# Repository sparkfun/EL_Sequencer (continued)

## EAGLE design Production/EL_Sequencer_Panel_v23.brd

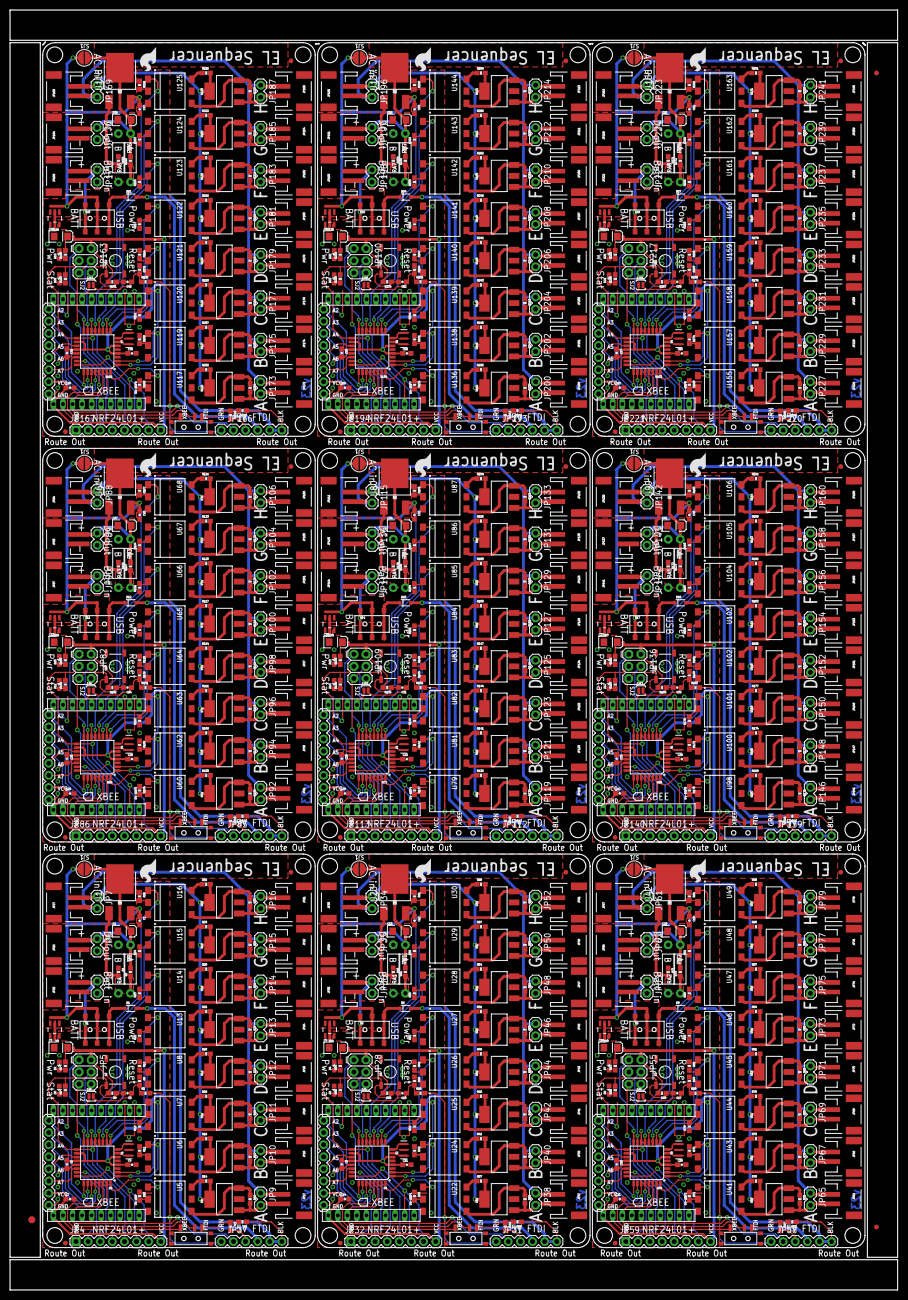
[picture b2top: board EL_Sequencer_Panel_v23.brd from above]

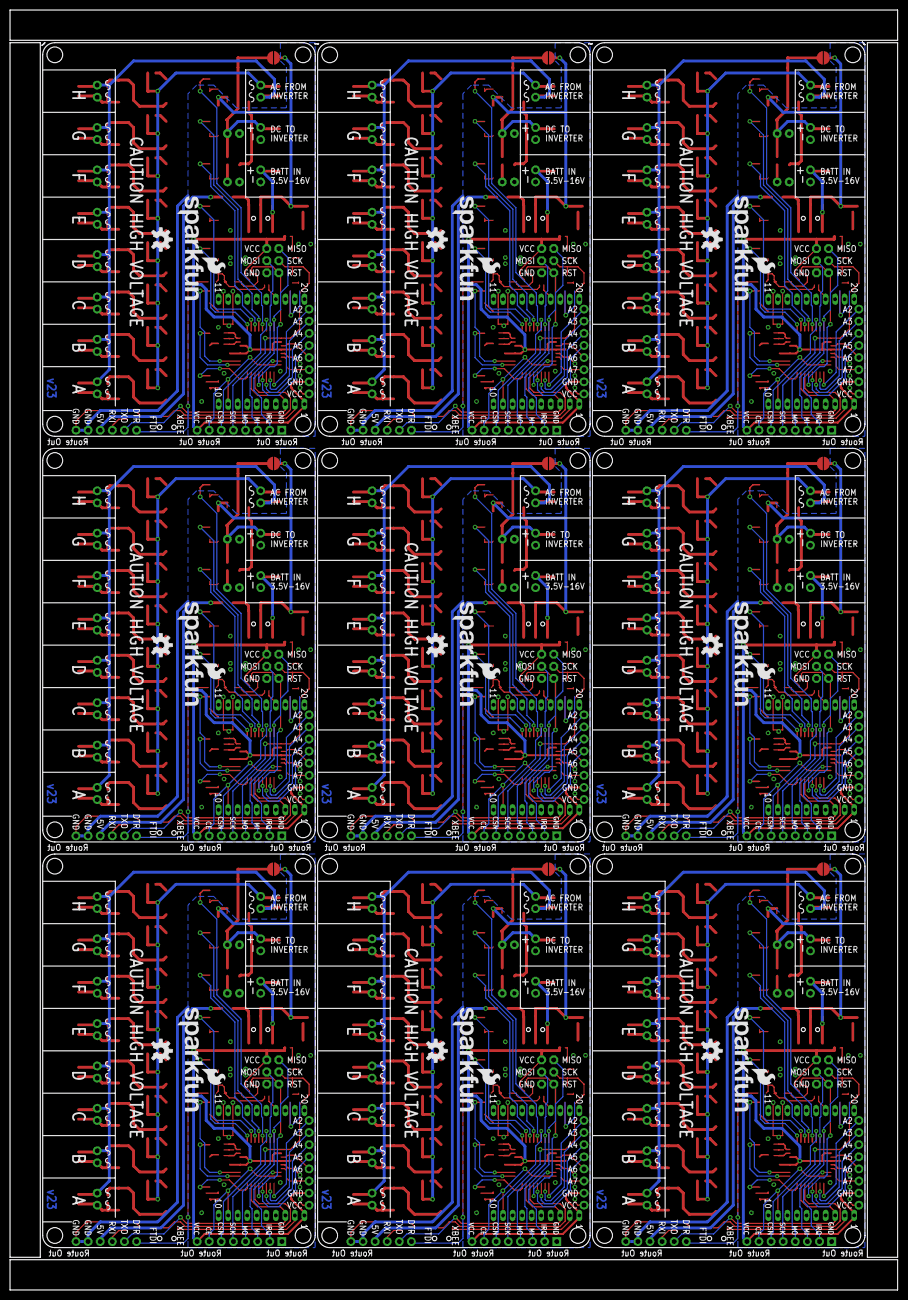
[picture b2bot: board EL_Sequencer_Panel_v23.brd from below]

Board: 2 copper layers, 186.2 x 268.5 mm, 957 parts (18 on the bottom side), 675 nets.

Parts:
C1, C4, C5, C6, C7, C8, C10, C11, C12, C14, C15, C17, C18, C19, C21, C22, C24, C25, C26, C28, C29, C31, C32, C33, C35, C36, C38, C39, C40, C42, C43, C45, C46, C47, C49, C50, C52, C53, C54, C56, C57, C59, C60, C61, C63: 0.1uF; 0603-CAP
C2, C3, C9, C13, C16, C20, C23, C27, C30, C34, C37, C41, C44, C48, C51, C55, C58, C62: 10uF; EIA3216
D1, D6, D9, D12, D15, D18, D21, D24, D27: PMEG4005EJ; SOD-323
D2, D4, D7, D10, D13, D16, D19, D22, D25: RED; LED-0603
D3, D5, D8, D11, D14, D17, D20, D23, D26: BLUE; LED-0603
E$1: FIDUCIAL-1.5X3
E$4, E$5: FIDUCIAL-1X2
FID1, FID2, FID3, FID4, FID5, FID6, FID7, FID8, FID9, FID10, FID11, FID12, FID13, FID14, FID15, FID16, FID17, FID18: FIDUCIAL1X2; FIDUCIAL-1X2
JP1, JP6, JP7, JP9, JP10, JP11, JP12, JP13, JP14, JP15, JP16, JP34, JP35, JP36, JP38, JP40, JP42, JP44, JP46, JP48, JP50, JP52, JP61, JP62, JP63, JP65, JP67, JP69, JP71, JP73, JP75, JP77, JP79, JP88, JP89, JP90, JP92, JP94, JP96, JP98, JP100, JP102, JP104, JP106, JP115, JP116, JP117, JP119, JP121, JP123, JP125, JP127, JP129, JP131, JP133, JP142, JP143, JP144, JP146, JP148, JP150, JP152, JP154, JP156, JP158, JP160, JP169, JP170, JP171, JP173, JP175, JP177, JP179, JP181, JP183, JP185, JP187, JP196, JP197, JP198, JP200, JP202, JP204, JP206, JP208, JP210, JP212, JP214, JP223, JP224, JP225, JP227, JP229, JP231, JP233, JP235, JP237, JP239, JP241: M02PTH; 1X02
JP2, JP53, JP80, JP107, JP134, JP161, JP188, JP215, JP242: I/O; 1X08_ROUND
JP3, JP31, JP58, JP85, JP112, JP139, JP166, JP193, JP220: 5V_FTDI; FTDI_BASIC
JP4, JP32, JP59, JP86, JP113, JP140, JP167, JP194, JP221: nRF24L01; 1X08
JP5, JP28, JP55, JP82, JP109, JP136, JP163, JP190, JP217: PROG; 2X3
JP8, JP54, JP81, JP108, JP135, JP162, JP189, JP216, JP243: SFE_LOGO_FLAME.2_INCH; SFE_LOGO_FLAME_.2
JP17, JP18, JP19, JP20, JP21, JP22, JP23, JP24, JP37, JP39, JP41, JP43, JP45, JP47, JP49, JP51, JP64, JP66, JP68, JP70, JP72, JP74, JP76, JP78, JP91, JP93, JP95, JP97, JP99, JP101, JP103, JP105, JP118, JP120, JP122, JP124, JP126, JP128, JP130, JP132, JP145, JP147, JP149, JP151, JP153, JP155, JP157, JP159, JP172, JP174, JP176, JP178, JP180, JP182, JP184, JP186, JP199, JP201, JP203, JP205, JP207, JP209, JP211, JP213, JP226, JP228, JP230, JP232, JP234, JP236, JP238, JP240: M02-JST-2MM-SMT; JST-2-SMD
JP25, JP33, JP60, JP87, JP114, JP141, JP168, JP195, JP222: Battery; JST-2-SMD
JP26, JP29, JP56, JP83, JP110, JP137, JP164, JP191, JP218: DC-OUTPUT; JST-2-SMD
JP27, JP30, JP57, JP84, JP111, JP138, JP165, JP192, JP219: AC-INPUT; JST-2-SMD
R1, R10, R11, R12, R13, R22, R23, R24, R25, R38, R40, R43, R46, R49, R52, R55, R58, R61, R71, R73, R76, R79, R82, R85, R88, R91, R94, R104, R106, R109, R112, R115, R118, R121, R124, R127, R137, R139, R142, R145, R148, R151, R154, R157, R160, R170, R172, R175, R178, R181, R184, R187, R190, R193, R203, R205, R208, R211, R214, R217, R220, R223, R226, R236, R238, R241, R244, R247, R250, R253, R256, R259, R269, R271, R274, R277, R280, R283, R286, R289, R292: 390; 0603-RES
R2, R41, R74, R107, R140, R173, R206, R239, R272: 240; 0603-RES
R3, R5, R7, R9, R34, R35, R64, R65, R67, R68, R97, R98, R100, R101, R130, R131, R133, R134, R163, R164, R166, R167, R196, R197, R199, R200, R229, R230, R232, R233, R262, R263, R265, R266, R295, R296: 1K; 0603-RES
R4, R6, R63, R66, R96, R99, R129, R132, R162, R165, R195, R198, R228, R231, R261, R264, R294, R297: 2K; 0603-RES
R8, R36, R69, R102, R135, R168, R201, R234, R267: 10K; 0603-RES
R14, R15, R16, R17, R18, R19, R20, R21, R26, R27, R28, R29, R30, R31, R32, R33, R37, R39, R42, R44, R45, R47, R48, R50, R51, R53, R54, R56, R57, R59, R60, R62, R70, R72, R75, R77, R78, R80, R81, R83, R84, R86, R87, R89, R90, R92, R93, R95, R103, R105, R108, R110, R111, R113, R114, R116, R117, R119, R120, R122, R123, R125, R126, R128, R136, R138, R141, R143, R144, R146, R147, R149, R150, R152, R153, R155, R156, R158, R159, R161, R169, R171, R174, R176, R177, R179, R180, R182, R183, R185, R186, R188, R189, R191, R192, R194, R202, R204, R207, R209, R210, R212, R213, R215, R216, R218, R219, R221, R222, R224, R225, R227, R235, R237, R240, R242, R243, R245, R246, R248, R249, R251, R252, R254, R255, R257, R258, R260, R268, R270, R273, R275, R276, R278, R279, R281, R282, R284, R285, R287, R288, R290, R291, R293: 330; 0603-RES
RA, RA1, RA2, RA3, RA4, RA5, RA6, RA7, RA8: A; AXIAL-0.4
RB, RB1, RB2, RB3, RB4, RB5, RB6, RB7, RB8: B; AXIAL-0.4
S1, S5, S8, S11, S14, S17, S20, S23, S26: DPDT; AYZ0202
S2, S4, S7, S10, S13, S16, S19, S22, S25: RESET; TACTILE-SWITCH-SMD
S3, S6, S9, S12, S15, S18, S21, S24, S27: SWITCH_SPDT; KPS-1290
SJ1, SJ3, SJ5, SJ7, SJ9, SJ11, SJ13, SJ15, SJ17: JUMPER-PAD-2-NOROUND; PAD-JUMPER-2-NO_YES_SILK_ROUND
SJ2, SJ4, SJ6, SJ8, SJ10, SJ12, SJ14, SJ16, SJ18: JUMPER-PAD-2-NOYES_SILK; PAD-JUMPER-2-NO_YES_SILK
U1, U23, U42, U61, U80, U99, U118, U137, U156: LM317; V-REG_DPACK
U2, U21, U40, U59, U78, U97, U116, U135, U154: MIC5219 3.3V; SOT23-5
U3, U4, U39, U58, U77, U96, U115, U134, U153: ATMEGA328P_TQFP; TQFP32-08
U4-DNP, U4-DNP1, U4-DNP2, U4-DNP3, U4-DNP4, U4-DNP5, U4-DNP6, U4-DNP7, U4-DNP8: XBEE HEADER; XBEE-LONGPAD
U5, U6, U7, U8, U13, U14, U15, U16, U22, U24, U25, U26, U27, U28, U29, U30, U41, U43, U44, U45, U46, U47, U48, U49, U60, U62, U63, U64, U65, U66, U67, U68, U79, U81, U82, U83, U84, U85, U86, U87, U98, U100, U101, U102, U103, U104, U105, U106, U117, U119, U120, U121, U122, U123, U124, U125, U136, U138, U139, U140, U141, U142, U143, U144, U155, U157, U158, U159, U160, U161, U162, U163: MOC3063S; DIP8SMD
U9, U10, U11, U12, U17, U18, U19, U20, U31, U32, U33, U34, U35, U36, U37, U38, U50, U51, U52, U53, U54, U55, U56, U57, U69, U70, U71, U72, U73, U74, U75, U76, U88, U89, U90, U91, U92, U93, U94, U95, U107, U108, U109, U110, U111, U112, U113, U114, U126, U127, U128, U129, U130, U131, U132, U133, U145, U146, U147, U148, U149, U150, U151, U152, U164, U165, U166, U167, U168, U169, U170, U171: Z0103MN; SOT223
U$1, U$12, U$18, U$24, U$30, U$36, U$42, U$48, U$54: OSHW-LOGOM; OSHW-LOGO-M
U$2, U$3, U$13, U$19, U$25, U$31, U$37, U$43, U$49: SFE_LOGO_NAME_FLAME.2_INCH; SFE_LOGO_NAME_FLAME_.2
U$4, U$5, U$6, U$7, U$8, U$9, U$10, U$11, U$14, U$15, U$16, U$17, U$20, U$21, U$22, U$23, U$26, U$27, U$28, U$29, U$32, U$33, U$34, U$35, U$38, U$39, U$40, U$41, U$44, U$45, U$46, U$47, U$50, U$51, U$52, U$53: STAND-OFF
Y1, Y2, Y3, Y4, Y5, Y6, Y7, Y8, Y9: 8MHZ; RESONATOR-SMD

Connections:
5VUSB: D1.A, JP3.VCC
5VUSB1: D6.A, JP31.VCC
5VUSB2: D9.A, JP58.VCC
5VUSB3: D12.A, JP85.VCC
5VUSB4: D15.A, JP112.VCC
5VUSB5: D18.A, JP139.VCC
5VUSB6: D21.A, JP166.VCC
5VUSB7: D24.A, JP193.VCC
5VUSB8: D27.A, JP220.VCC
ADC_1: JP53.8, U4.25
ADC_2: JP2.8, U3.25
ADC_3: JP2.7, U3.26
ADC_4: JP2.6, U3.27
ADC_5: JP2.5, U3.28
ADC_6: JP53.7, U4.26
ADC_6*: JP2.4, U3.19
ADC_6*1: JP53.4, U4.19
ADC_6*2: JP80.4, U39.19
ADC_6*3: JP107.4, U58.19
ADC_6*4: JP134.4, U77.19
ADC_6*5: JP161.4, U96.19
ADC_6*6: JP188.4, U115.19
ADC_6*7: JP215.4, U134.19
ADC_6*8: JP242.4, U153.19
ADC_7: JP53.6, U4.27
ADC_7*: JP2.3, U3.22
ADC_7*1: JP53.3, U4.22
ADC_7*2: JP80.3, U39.22
ADC_7*3: JP107.3, U58.22
ADC_7*4: JP134.3, U77.22
ADC_7*5: JP161.3, U96.22
ADC_7*6: JP188.3, U115.22
ADC_7*7: JP215.3, U134.22
ADC_7*8: JP242.3, U153.22
ADC_8: JP53.5, U4.28
ADC_9: JP80.8, U39.25
ADC_10: JP80.7, U39.26
ADC_11: JP80.6, U39.27
ADC_12: JP80.5, U39.28
ADC_13: JP107.8, U58.25
ADC_14: JP107.7, U58.26
ADC_15: JP107.6, U58.27
ADC_16: JP107.5, U58.28
ADC_17: JP134.8, U77.25
ADC_18: JP134.7, U77.26
ADC_19: JP134.6, U77.27
ADC_20: JP134.5, U77.28
ADC_21: JP161.8, U96.25
ADC_22: JP161.7, U96.26
ADC_23: JP161.6, U96.27
ADC_24: JP161.5, U96.28
ADC_25: JP188.8, U115.25
ADC_26: JP188.7, U115.26
ADC_27: JP188.6, U115.27
ADC_28: JP188.5, U115.28
ADC_29: JP215.8, U134.25
ADC_30: JP215.7, U134.26
ADC_31: JP215.6, U134.27
ADC_32: JP215.5, U134.28
ADC_33: JP242.8, U153.25
ADC_34: JP242.7, U153.26
ADC_35: JP242.6, U153.27
ADC_36: JP242.5, U153.28
CE/SLEEP: JP4.7, U3.24, U4-DNP.9
CE/SLEEP1: JP32.7, U4.24, U4-DNP1.9
CE/SLEEP2: JP59.7, U4-DNP2.9, U39.24
CE/SLEEP3: JP86.7, U4-DNP3.9, U58.24
CE/SLEEP4: JP113.7, U4-DNP4.9, U77.24
CE/SLEEP5: JP140.7, U4-DNP5.9, U96.24
CE/SLEEP6: JP167.7, U4-DNP6.9, U115.24
CE/SLEEP7: JP194.7, U4-DNP7.9, U134.24
CE/SLEEP8: JP221.7, U4-DNP8.9, U153.24
CSN: JP4.6, U3.14
CSN1: JP32.6, U4.14
CSN2: JP59.6, U39.14
CSN3: JP86.6, U58.14
CSN4: JP113.6, U77.14
CSN5: JP140.6, U96.14
CSN6: JP167.6, U115.14
CSN7: JP194.6, U134.14
CSN8: JP221.6, U153.14
DIO_VBUS: D1.C, S1.3, S1.6
DIO_VBUS1: D6.C, S5.3, S5.6
DIO_VBUS2: D9.C, S8.3, S8.6
DIO_VBUS3: D12.C, S11.3, S11.6
DIO_VBUS4: D15.C, S14.3, S14.6
DIO_VBUS5: D18.C, S17.3, S17.6
DIO_VBUS6: D21.C, S20.3, S20.6
DIO_VBUS7: D24.C, S23.3, S23.6
DIO_VBUS8: D27.C, S26.3, S26.6
DTR: C5.1, R5.1, R6.2, SJ2.2
DTR1: C10.1, R65.1, R66.2, SJ4.2
DTR2: C17.1, R98.1, R99.2, SJ6.2
DTR3: C24.1, R131.1, R132.2, SJ8.2
DTR4: C31.1, R164.1, R165.2, SJ10.2
DTR5: C38.1, R197.1, R198.2, SJ12.2
DTR6: C45.1, R230.1, R231.2, SJ14.2
DTR7: C52.1, R263.1, R264.2, SJ16.2
DTR8: C59.1, R296.1, R297.2, SJ18.2
EL_A: U3.32, U5.1
EL_A1: U4.32, U22.1
EL_A2: U39.32, U41.1
EL_A3: U58.32, U60.1
EL_A4: U77.32, U79.1
EL_A5: U96.32, U98.1
EL_A6: U115.32, U117.1
EL_A7: U134.32, U136.1
EL_A8: U153.32, U155.1
EL_B: U3.1, U6.1
EL_B1: U4.1, U24.1
EL_B2: U39.1, U43.1
EL_B3: U58.1, U62.1
EL_B4: U77.1, U81.1
EL_B5: U96.1, U100.1
EL_B6: U115.1, U119.1
EL_B7: U134.1, U138.1
EL_B8: U153.1, U157.1
EL_C: U3.2, U7.1
EL_C1: U4.2, U25.1
EL_C2: U39.2, U44.1
EL_C3: U58.2, U63.1
EL_C4: U77.2, U82.1
EL_C5: U96.2, U101.1
EL_C6: U115.2, U120.1
EL_C7: U134.2, U139.1
EL_C8: U153.2, U158.1
EL_D: U3.9, U8.1
EL_D1: U4.9, U26.1
EL_D2: U39.9, U45.1
EL_D3: U58.9, U64.1
EL_D4: U77.9, U83.1
EL_D5: U96.9, U102.1
EL_D6: U115.9, U121.1
EL_D7: U134.9, U140.1
EL_D8: U153.9, U159.1
EL_E: U3.10, U13.1
EL_E1: U4.10, U27.1
EL_E2: U39.10, U46.1
EL_E3: U58.10, U65.1
EL_E4: U77.10, U84.1
EL_E5: U96.10, U103.1
EL_E6: U115.10, U122.1
EL_E7: U134.10, U141.1
EL_E8: U153.10, U160.1
EL_F: U3.11, U14.1
EL_F1: U4.11, U28.1
EL_F2: U39.11, U47.1
EL_F3: U58.11, U66.1
EL_F4: U77.11, U85.1
EL_F5: U96.11, U104.1
EL_F6: U115.11, U123.1
EL_F7: U134.11, U142.1
EL_F8: U153.11, U161.1
EL_G: U3.12, U15.1
EL_G1: U4.12, U29.1
EL_G2: U39.12, U48.1
EL_G3: U58.12, U67.1
EL_G4: U77.12, U86.1
EL_G5: U96.12, U105.1
EL_G6: U115.12, U124.1
EL_G7: U134.12, U143.1
EL_G8: U153.12, U162.1
EL_H: U3.13, U16.1
EL_H1: U4.13, U30.1
EL_H2: U39.13, U49.1
EL_H3: U58.13, U68.1
EL_H4: U77.13, U87.1
EL_H5: U96.13, U106.1
EL_H6: U115.13, U125.1
EL_H7: U134.13, U144.1
EL_H8: U153.13, U163.1
FTDI_DTR: JP3.DTR, R5.2
FTDI_DTR1: JP31.DTR, R65.2
FTDI_DTR2: JP58.DTR, R98.2
FTDI_DTR3: JP85.DTR, R131.2
FTDI_DTR4: JP112.DTR, R164.2
FTDI_DTR5: JP139.DTR, R197.2
FTDI_DTR6: JP166.DTR, R230.2
FTDI_DTR7: JP193.DTR, R263.2
FTDI_DTR8: JP220.DTR, R296.2
FTDI_RXI: JP3.TXO, R3.2
FTDI_RXI1: JP31.TXO, R64.2
FTDI_RXI2: JP58.TXO, R97.2
FTDI_RXI3: JP85.TXO, R130.2
FTDI_RXI4: JP112.TXO, R163.2
FTDI_RXI5: JP139.TXO, R196.2
FTDI_RXI6: JP166.TXO, R229.2
FTDI_RXI7: JP193.TXO, R262.2
FTDI_RXI8: JP220.TXO, R295.2
GND: C1.2, C2.C, C3.C, C4.2, C6.2, C7.2, D2.C, D3.C, JP1.2, JP2.1, JP3.CTS, JP3.GND, JP4.1, JP5.6, JP6.2, JP25.1, JP26.1, R1.1, R4.1, R6.1, R10.1, R11.1, R12.1, R13.1, R22.1, R23.1, R24.1, R25.1, RB.P$1, S2.3, U2.2, U3.3, U3.5, U3.21, U4-DNP.10, Y1.2
GND1: C8.2, C9.C, C11.2, C12.2, C13.C, C14.2, D4.C, D5.C, JP28.6, JP29.1, JP31.CTS, JP31.GND, JP32.1, JP33.1, JP35.2, JP36.2, JP53.1, R38.1, R40.1, R43.1, R46.1, R49.1, R52.1, R55.1, R58.1, R61.1, R63.1, R66.1, RB1.P$1, S4.3, U4.3, U4.5, U4.21, U4-DNP1.10, U21.2, Y2.2
GND2: C15.2, C16.C, C18.2, C19.2, C20.C, C21.2, D7.C, D8.C, JP55.6, JP56.1, JP58.CTS, JP58.GND, JP59.1, JP60.1, JP62.2, JP63.2, JP80.1, R71.1, R73.1, R76.1, R79.1, R82.1, R85.1, R88.1, R91.1, R94.1, R96.1, R99.1, RB2.P$1, S7.3, U4-DNP2.10, U39.3, U39.5, U39.21, U40.2, Y3.2
GND3: C22.2, C23.C, C25.2, C26.2, C27.C, C28.2, D10.C, D11.C, JP82.6, JP83.1, JP85.CTS, JP85.GND, JP86.1, JP87.1, JP89.2, JP90.2, JP107.1, R104.1, R106.1, R109.1, R112.1, R115.1, R118.1, R121.1, R124.1, R127.1, R129.1, R132.1, RB3.P$1, S10.3, U4-DNP3.10, U58.3, U58.5, U58.21, U59.2, Y4.2
GND4: C29.2, C30.C, C32.2, C33.2, C34.C, C35.2, D13.C, D14.C, JP109.6, JP110.1, JP112.CTS, JP112.GND, JP113.1, JP114.1, JP116.2, JP117.2, JP134.1, R137.1, R139.1, R142.1, R145.1, R148.1, R151.1, R154.1, R157.1, R160.1, R162.1, R165.1, RB4.P$1, S13.3, U4-DNP4.10, U77.3, U77.5, U77.21, U78.2, Y5.2
GND5: C36.2, C37.C, C39.2, C40.2, C41.C, C42.2, D16.C, D17.C, JP136.6, JP137.1, JP139.CTS, JP139.GND, JP140.1, JP141.1, JP143.2, JP144.2, JP161.1, R170.1, R172.1, R175.1, R178.1, R181.1, R184.1, R187.1, R190.1, R193.1, R195.1, R198.1, RB5.P$1, S16.3, U4-DNP5.10, U96.3, U96.5, U96.21, U97.2, Y6.2
GND6: C43.2, C44.C, C46.2, C47.2, C48.C, C49.2, D19.C, D20.C, JP163.6, JP164.1, JP166.CTS, JP166.GND, JP167.1, JP168.1, JP170.2, JP171.2, JP188.1, R203.1, R205.1, R208.1, R211.1, R214.1, R217.1, R220.1, R223.1, R226.1, R228.1, R231.1, RB6.P$1, S19.3, U4-DNP6.10, U115.3, U115.5, U115.21, U116.2, Y7.2
GND7: C50.2, C51.C, C53.2, C54.2, C55.C, C56.2, D22.C, D23.C, JP190.6, JP191.1, JP193.CTS, JP193.GND, JP194.1, JP195.1, JP197.2, JP198.2, JP215.1, R236.1, R238.1, R241.1, R244.1, R247.1, R250.1, R253.1, R256.1, R259.1, R261.1, R264.1, RB7.P$1, S22.3, U4-DNP7.10, U134.3, U134.5, U134.21, U135.2, Y8.2
GND8: C57.2, C58.C, C60.2, C61.2, C62.C, C63.2, D25.C, D26.C, JP217.6, JP218.1, JP220.CTS, JP220.GND, JP221.1, JP222.1, JP224.2, JP225.2, JP242.1, R269.1, R271.1, R274.1, R277.1, R280.1, R283.1, R286.1, R289.1, R292.1, R294.1, R297.1, RB8.P$1, S25.3, U4-DNP8.10, U153.3, U153.5, U153.21, U154.2, Y9.2
HV: JP7.1, JP27.2, R14.2, R16.2, R18.2, R20.2, R26.2, R28.2, R30.2, R32.2, U9.4, U10.4, U11.4, U12.4, U17.4, U18.4, U19.4, U20.4
HV1: JP30.2, JP34.1, R37.2, R42.2, R45.2, R48.2, R51.2, R54.2, R57.2, R60.2, U31.4, U32.4, U33.4, U34.4, U35.4, U36.4, U37.4, U38.4
HV2: JP57.2, JP61.1, R70.2, R75.2, R78.2, R81.2, R84.2, R87.2, R90.2, R93.2, U50.4, U51.4, U52.4, U53.4, U54.4, U55.4, U56.4, U57.4
HV3: JP84.2, JP88.1, R103.2, R108.2, R111.2, R114.2, R117.2, R120.2, R123.2, R126.2, U69.4, U70.4, U71.4, U72.4, U73.4, U74.4, U75.4, U76.4
HV4: JP111.2, JP115.1, R136.2, R141.2, R144.2, R147.2, R150.2, R153.2, R156.2, R159.2, U88.4, U89.4, U90.4, U91.4, U92.4, U93.4, U94.4, U95.4
HV5: JP138.2, JP142.1, R169.2, R174.2, R177.2, R180.2, R183.2, R186.2, R189.2, R192.2, U107.4, U108.4, U109.4, U110.4, U111.4, U112.4, U113.4, U114.4
HV6: JP165.2, JP169.1, R202.2, R207.2, R210.2, R213.2, R216.2, R219.2, R222.2, R225.2, U126.4, U127.4, U128.4, U129.4, U130.4, U131.4, U132.4, U133.4
HV7: JP192.2, JP196.1, R235.2, R240.2, R243.2, R246.2, R249.2, R252.2, R255.2, R258.2, U145.4, U146.4, U147.4, U148.4, U149.4, U150.4, U151.4, U152.4
HV8: JP219.2, JP223.1, R268.2, R273.2, R276.2, R279.2, R282.2, R285.2, R288.2, R291.2, U164.4, U165.4, U166.4, U167.4, U168.4, U169.4, U170.4, U171.4
HVGND: JP7.2, JP9.1, JP10.1, JP11.1, JP12.1, JP13.1, JP14.1, JP15.1, JP16.1, JP17.1, JP18.1, JP19.1, JP20.1, JP21.1, JP22.1, JP23.1, JP24.1, JP27.1
HVGND1: JP30.1, JP34.2, JP37.1, JP38.1, JP39.1, JP40.1, JP41.1, JP42.1, JP43.1, JP44.1, JP45.1, JP46.1, JP47.1, JP48.1, JP49.1, JP50.1, JP51.1, JP52.1
HVGND2: JP57.1, JP61.2, JP64.1, JP65.1, JP66.1, JP67.1, JP68.1, JP69.1, JP70.1, JP71.1, JP72.1, JP73.1, JP74.1, JP75.1, JP76.1, JP77.1, JP78.1, JP79.1
HVGND3: JP84.1, JP88.2, JP91.1, JP92.1, JP93.1, JP94.1, JP95.1, JP96.1, JP97.1, JP98.1, JP99.1, JP100.1, JP101.1, JP102.1, JP103.1, JP104.1, JP105.1, JP106.1
HVGND4: JP111.1, JP115.2, JP118.1, JP119.1, JP120.1, JP121.1, JP122.1, JP123.1, JP124.1, JP125.1, JP126.1, JP127.1, JP128.1, JP129.1, JP130.1, JP131.1, JP132.1, JP133.1
HVGND5: JP138.1, JP142.2, JP145.1, JP146.1, JP147.1, JP148.1, JP149.1, JP150.1, JP151.1, JP152.1, JP153.1, JP154.1, JP155.1, JP156.1, JP157.1, JP158.1, JP159.1, JP160.1
HVGND6: JP165.1, JP169.2, JP172.1, JP173.1, JP174.1, JP175.1, JP176.1, JP177.1, JP178.1, JP179.1, JP180.1, JP181.1, JP182.1, JP183.1, JP184.1, JP185.1, JP186.1, JP187.1
HVGND7: JP192.1, JP196.2, JP199.1, JP200.1, JP201.1, JP202.1, JP203.1, JP204.1, JP205.1, JP206.1, JP207.1, JP208.1, JP209.1, JP210.1, JP211.1, JP212.1, JP213.1, JP214.1
HVGND8: JP219.1, JP223.2, JP226.1, JP227.1, JP228.1, JP229.1, JP230.1, JP231.1, JP232.1, JP233.1, JP234.1, JP235.1, JP236.1, JP237.1, JP238.1, JP239.1, JP240.1, JP241.1
INV: C2.A, JP6.1, JP26.2, R2.2, RA.P$2, SJ1.2, U1.4
INV1: C13.A, JP29.2, JP35.1, R41.2, RA1.P$2, SJ3.2, U23.4
INV2: C20.A, JP56.2, JP62.1, R74.2, RA2.P$2, SJ5.2, U42.4
INV3: C27.A, JP83.2, JP89.1, R107.2, RA3.P$2, SJ7.2, U61.4
INV4: C34.A, JP110.2, JP116.1, R140.2, RA4.P$2, SJ9.2, U80.4
INV5: C41.A, JP137.2, JP143.1, R173.2, RA5.P$2, SJ11.2, U99.4
INV6: C48.A, JP164.2, JP170.1, R206.2, RA6.P$2, SJ13.2, U118.4
INV7: C55.A, JP191.2, JP197.1, R239.2, RA7.P$2, SJ15.2, U137.4
INV8: C62.A, JP218.2, JP224.1, R272.2, RA8.P$2, SJ17.2, U156.4
IRQ: JP4.2, U3.23
IRQ1: JP32.2, U4.23
IRQ2: JP59.2, U39.23
IRQ3: JP86.2, U58.23
IRQ4: JP113.2, U77.23
IRQ5: JP140.2, U96.23
IRQ6: JP167.2, U115.23
IRQ7: JP194.2, U134.23
IRQ8: JP221.2, U153.23
MISO: JP4.3, JP5.1, U3.16
MISO1: JP28.1, JP32.3, U4.16
MISO2: JP55.1, JP59.3, U39.16
MISO3: JP82.1, JP86.3, U58.16
MISO4: JP109.1, JP113.3, U77.16
MISO5: JP136.1, JP140.3, U96.16
MISO6: JP163.1, JP167.3, U115.16
MISO7: JP190.1, JP194.3, U134.16
MISO8: JP217.1, JP221.3, U153.16
MOSI: JP4.4, JP5.4, U3.15
MOSI1: JP28.4, JP32.4, U4.15
MOSI2: JP55.4, JP59.4, U39.15
MOSI3: JP82.4, JP86.4, U58.15
MOSI4: JP109.4, JP113.4, U77.15
MOSI5: JP136.4, JP140.4, U96.15
MOSI6: JP163.4, JP167.4, U115.15
MOSI7: JP190.4, JP194.4, U134.15
MOSI8: JP217.4, JP221.4, U153.15
unnamed: U3.7, Y1.1
unnamed: R17.1, U6.4, U10.3
unnamed: R11.2, U6.2
unnamed: D2.A, R7.1
unnamed: R16.1, U6.6
unnamed: U3.8, Y1.3
unnamed: R10.2, U5.2
unnamed: SJ2.1, U4-DNP.17
unnamed: JP10.2, JP18.2, R17.2, U10.1
unnamed: R19.1, U7.4, U11.3
unnamed: R14.1, U5.6
unnamed: R12.2, U7.2
unnamed: D4.A, R34.1
unnamed: D3.A, R9.1
unnamed: R18.1, U7.6
unnamed: JP11.2, JP19.2, R19.2, U11.1
unnamed: R21.1, U8.4, U12.3
unnamed: R13.2, U8.2
unnamed: R20.1, U8.6
unnamed: JP12.2, JP20.2, R21.2, U12.1
unnamed: JP9.2, JP17.2, R15.2, U9.1
unnamed: R27.1, U13.4, U17.3
unnamed: R22.2, U13.2
unnamed: R26.1, U13.6
unnamed: JP13.2, JP24.2, R27.2, U17.1
unnamed: R29.1, U14.4, U18.3
unnamed: R23.2, U14.2
unnamed: R28.1, U14.6
unnamed: JP14.2, JP23.2, R29.2, U18.1
unnamed: R31.1, U15.4, U19.3
unnamed: R24.2, U15.2
unnamed: R30.1, U15.6
unnamed: JP15.2, JP22.2, R31.2, U19.1
unnamed: R33.1, U16.4, U20.3
unnamed: R25.2, U16.2
unnamed: R32.1, U16.6
unnamed: JP16.2, JP21.2, R33.2, U20.1
unnamed: R1.2, R2.1, RA.P$1, RB.P$2, U1.1
unnamed: D5.A, R35.1
unnamed: U4.7, Y2.1
unnamed: U4.8, Y2.3
unnamed: R39.1, U22.4, U31.3
unnamed: R38.2, U22.2
unnamed: R37.1, U22.6
unnamed: JP37.2, JP38.2, R39.2, U31.1
unnamed: R44.1, U24.4, U32.3
unnamed: R43.2, U24.2
unnamed: R42.1, U24.6
unnamed: JP39.2, JP40.2, R44.2, U32.1
unnamed: R47.1, U25.4, U33.3
unnamed: R46.2, U25.2
unnamed: R45.1, U25.6
unnamed: JP41.2, JP42.2, R47.2, U33.1
unnamed: R50.1, U26.4, U34.3
unnamed: R49.2, U26.2
unnamed: R48.1, U26.6
unnamed: JP43.2, JP44.2, R50.2, U34.1
unnamed: R53.1, U27.4, U35.3
unnamed: R52.2, U27.2
unnamed: R51.1, U27.6
unnamed: JP45.2, JP46.2, R53.2, U35.1
unnamed: R56.1, U28.4, U36.3
unnamed: R55.2, U28.2
unnamed: R54.1, U28.6
unnamed: JP47.2, JP48.2, R56.2, U36.1
unnamed: R59.1, U29.4, U37.3
unnamed: R58.2, U29.2
unnamed: R57.1, U29.6
unnamed: JP49.2, JP50.2, R59.2, U37.1
unnamed: R62.1, U30.4, U38.3
unnamed: R61.2, U30.2
unnamed: R60.1, U30.6
unnamed: JP51.2, JP52.2, R62.2, U38.1
unnamed: SJ4.1, U4-DNP1.17
unnamed: R40.2, R41.1, RA1.P$1, RB1.P$2, U23.1
unnamed: D7.A, R67.1
unnamed: D8.A, R68.1
unnamed: U39.7, Y3.1
unnamed: U39.8, Y3.3
unnamed: R72.1, U41.4, U50.3
unnamed: R71.2, U41.2
unnamed: R70.1, U41.6
unnamed: JP64.2, JP65.2, R72.2, U50.1
unnamed: R77.1, U43.4, U51.3
unnamed: R76.2, U43.2
unnamed: R75.1, U43.6
unnamed: JP66.2, JP67.2, R77.2, U51.1
unnamed: R80.1, U44.4, U52.3
unnamed: R79.2, U44.2
unnamed: R78.1, U44.6
unnamed: JP68.2, JP69.2, R80.2, U52.1
unnamed: R83.1, U45.4, U53.3
unnamed: R82.2, U45.2
unnamed: R81.1, U45.6
unnamed: JP70.2, JP71.2, R83.2, U53.1
unnamed: R86.1, U46.4, U54.3
unnamed: R85.2, U46.2
unnamed: R84.1, U46.6
unnamed: JP72.2, JP73.2, R86.2, U54.1
unnamed: R89.1, U47.4, U55.3
unnamed: R88.2, U47.2
unnamed: R87.1, U47.6
unnamed: JP74.2, JP75.2, R89.2, U55.1
unnamed: R92.1, U48.4, U56.3
unnamed: R91.2, U48.2
unnamed: R90.1, U48.6
unnamed: JP76.2, JP77.2, R92.2, U56.1
unnamed: R95.1, U49.4, U57.3
unnamed: R94.2, U49.2
unnamed: R93.1, U49.6
unnamed: JP78.2, JP79.2, R95.2, U57.1
unnamed: SJ6.1, U4-DNP2.17
unnamed: R73.2, R74.1, RA2.P$1, RB2.P$2, U42.1
unnamed: D10.A, R100.1
unnamed: D11.A, R101.1
unnamed: U58.7, Y4.1
unnamed: R15.1, U5.4, U9.3
unnamed: U58.8, Y4.3
unnamed: R105.1, U60.4, U69.3
unnamed: R104.2, U60.2
unnamed: R103.1, U60.6
unnamed: JP91.2, JP92.2, R105.2, U69.1
unnamed: R110.1, U62.4, U70.3
unnamed: R109.2, U62.2
unnamed: R108.1, U62.6
unnamed: JP93.2, JP94.2, R110.2, U70.1
unnamed: R113.1, U63.4, U71.3
unnamed: R112.2, U63.2
unnamed: R111.1, U63.6
unnamed: JP95.2, JP96.2, R113.2, U71.1
unnamed: R116.1, U64.4, U72.3
unnamed: R115.2, U64.2
unnamed: R114.1, U64.6
unnamed: JP97.2, JP98.2, R116.2, U72.1
unnamed: R119.1, U65.4, U73.3
unnamed: R118.2, U65.2
unnamed: R117.1, U65.6
unnamed: JP99.2, JP100.2, R119.2, U73.1
unnamed: R122.1, U66.4, U74.3
unnamed: R121.2, U66.2
unnamed: R120.1, U66.6
unnamed: JP101.2, JP102.2, R122.2, U74.1
unnamed: R125.1, U67.4, U75.3
unnamed: R124.2, U67.2
unnamed: R123.1, U67.6
unnamed: JP103.2, JP104.2, R125.2, U75.1
unnamed: R128.1, U68.4, U76.3
unnamed: R127.2, U68.2
unnamed: R126.1, U68.6
unnamed: JP105.2, JP106.2, R128.2, U76.1
unnamed: SJ8.1, U4-DNP3.17
unnamed: R106.2, R107.1, RA3.P$1, RB3.P$2, U61.1
unnamed: D13.A, R133.1
unnamed: D14.A, R134.1
unnamed: U77.7, Y5.1
unnamed: U77.8, Y5.3
unnamed: R138.1, U79.4, U88.3
unnamed: R137.2, U79.2
unnamed: R136.1, U79.6
unnamed: JP118.2, JP119.2, R138.2, U88.1
unnamed: R143.1, U81.4, U89.3
unnamed: R142.2, U81.2
unnamed: R141.1, U81.6
unnamed: JP120.2, JP121.2, R143.2, U89.1
unnamed: R146.1, U82.4, U90.3
unnamed: R145.2, U82.2
unnamed: R144.1, U82.6
unnamed: JP122.2, JP123.2, R146.2, U90.1
unnamed: R149.1, U83.4, U91.3
unnamed: R148.2, U83.2
unnamed: R147.1, U83.6
unnamed: JP124.2, JP125.2, R149.2, U91.1
unnamed: R152.1, U84.4, U92.3
unnamed: R151.2, U84.2
unnamed: R150.1, U84.6
unnamed: JP126.2, JP127.2, R152.2, U92.1
unnamed: R155.1, U85.4, U93.3
unnamed: R154.2, U85.2
unnamed: R153.1, U85.6
unnamed: JP128.2, JP129.2, R155.2, U93.1
unnamed: R158.1, U86.4, U94.3
unnamed: R157.2, U86.2
unnamed: R156.1, U86.6
unnamed: JP130.2, JP131.2, R158.2, U94.1
unnamed: R161.1, U87.4, U95.3
unnamed: R160.2, U87.2
unnamed: R159.1, U87.6
unnamed: JP132.2, JP133.2, R161.2, U95.1
unnamed: SJ10.1, U4-DNP4.17
unnamed: R139.2, R140.1, RA4.P$1, RB4.P$2, U80.1
unnamed: D16.A, R166.1
unnamed: D17.A, R167.1
unnamed: U96.7, Y6.1
unnamed: U96.8, Y6.3
unnamed: R171.1, U98.4, U107.3
unnamed: R170.2, U98.2
unnamed: R169.1, U98.6
unnamed: JP145.2, JP146.2, R171.2, U107.1
unnamed: R176.1, U100.4, U108.3
unnamed: R175.2, U100.2
unnamed: R174.1, U100.6
unnamed: JP147.2, JP148.2, R176.2, U108.1
unnamed: R179.1, U101.4, U109.3
unnamed: R178.2, U101.2
unnamed: R177.1, U101.6
unnamed: JP149.2, JP150.2, R179.2, U109.1
unnamed: R182.1, U102.4, U110.3
unnamed: R181.2, U102.2
unnamed: R180.1, U102.6
unnamed: JP151.2, JP152.2, R182.2, U110.1
unnamed: R185.1, U103.4, U111.3
unnamed: R184.2, U103.2
unnamed: R183.1, U103.6
unnamed: JP153.2, JP154.2, R185.2, U111.1
unnamed: R188.1, U104.4, U112.3
unnamed: R187.2, U104.2
unnamed: R186.1, U104.6
unnamed: JP155.2, JP156.2, R188.2, U112.1
unnamed: R191.1, U105.4, U113.3
unnamed: R190.2, U105.2
unnamed: R189.1, U105.6
unnamed: JP157.2, JP158.2, R191.2, U113.1
unnamed: R194.1, U106.4, U114.3
unnamed: R193.2, U106.2
unnamed: R192.1, U106.6
unnamed: JP159.2, JP160.2, R194.2, U114.1
unnamed: SJ12.1, U4-DNP5.17
unnamed: R172.2, R173.1, RA5.P$1, RB5.P$2, U99.1
unnamed: D19.A, R199.1
unnamed: D20.A, R200.1
unnamed: U115.7, Y7.1
unnamed: U115.8, Y7.3
unnamed: R204.1, U117.4, U126.3
unnamed: R203.2, U117.2
unnamed: R202.1, U117.6
unnamed: JP172.2, JP173.2, R204.2, U126.1
unnamed: R209.1, U119.4, U127.3
unnamed: R208.2, U119.2
unnamed: R207.1, U119.6
unnamed: JP174.2, JP175.2, R209.2, U127.1
unnamed: R212.1, U120.4, U128.3
unnamed: R211.2, U120.2
unnamed: R210.1, U120.6
unnamed: JP176.2, JP177.2, R212.2, U128.1
unnamed: R215.1, U121.4, U129.3
unnamed: R214.2, U121.2
unnamed: R213.1, U121.6
unnamed: JP178.2, JP179.2, R215.2, U129.1
unnamed: R218.1, U122.4, U130.3
unnamed: R217.2, U122.2
unnamed: R216.1, U122.6
unnamed: JP180.2, JP181.2, R218.2, U130.1
unnamed: R221.1, U123.4, U131.3
unnamed: R220.2, U123.2
unnamed: R219.1, U123.6
unnamed: JP182.2, JP183.2, R221.2, U131.1
unnamed: R224.1, U124.4, U132.3
unnamed: R223.2, U124.2
unnamed: R222.1, U124.6
unnamed: JP184.2, JP185.2, R224.2, U132.1
unnamed: R227.1, U125.4, U133.3
unnamed: R226.2, U125.2
unnamed: R225.1, U125.6
unnamed: JP186.2, JP187.2, R227.2, U133.1
unnamed: SJ14.1, U4-DNP6.17
unnamed: R205.2, R206.1, RA6.P$1, RB6.P$2, U118.1
unnamed: D22.A, R232.1
unnamed: D23.A, R233.1
unnamed: U134.7, Y8.1
unnamed: U134.8, Y8.3
unnamed: R237.1, U136.4, U145.3
unnamed: R236.2, U136.2
unnamed: R235.1, U136.6
unnamed: JP199.2, JP200.2, R237.2, U145.1
unnamed: R242.1, U138.4, U146.3
unnamed: R241.2, U138.2
unnamed: R240.1, U138.6
unnamed: JP201.2, JP202.2, R242.2, U146.1
unnamed: R245.1, U139.4, U147.3
unnamed: R244.2, U139.2
unnamed: R243.1, U139.6
unnamed: JP203.2, JP204.2, R245.2, U147.1
unnamed: R248.1, U140.4, U148.3
unnamed: R247.2, U140.2
unnamed: R246.1, U140.6
unnamed: JP205.2, JP206.2, R248.2, U148.1
unnamed: R251.1, U141.4, U149.3
unnamed: R250.2, U141.2
unnamed: R249.1, U141.6
unnamed: JP207.2, JP208.2, R251.2, U149.1
unnamed: R254.1, U142.4, U150.3
unnamed: R253.2, U142.2
unnamed: R252.1, U142.6
unnamed: JP209.2, JP210.2, R254.2, U150.1
unnamed: R257.1, U143.4, U151.3
unnamed: R256.2, U143.2
unnamed: R255.1, U143.6
unnamed: JP211.2, JP212.2, R257.2, U151.1
unnamed: R260.1, U144.4, U152.3
unnamed: R259.2, U144.2
unnamed: R258.1, U144.6
unnamed: JP213.2, JP214.2, R260.2, U152.1
unnamed: SJ16.1, U4-DNP7.17
unnamed: R238.2, R239.1, RA7.P$1, RB7.P$2, U137.1
unnamed: D25.A, R265.1
unnamed: D26.A, R266.1
unnamed: U153.7, Y9.1
unnamed: U153.8, Y9.3
unnamed: R270.1, U155.4, U164.3
unnamed: R269.2, U155.2
unnamed: R268.1, U155.6
unnamed: JP226.2, JP227.2, R270.2, U164.1
unnamed: R275.1, U157.4, U165.3
unnamed: R274.2, U157.2
unnamed: R273.1, U157.6
unnamed: JP228.2, JP229.2, R275.2, U165.1
unnamed: R278.1, U158.4, U166.3
unnamed: R277.2, U158.2
unnamed: R276.1, U158.6
unnamed: JP230.2, JP231.2, R278.2, U166.1
unnamed: R281.1, U159.4, U167.3
unnamed: R280.2, U159.2
unnamed: R279.1, U159.6
unnamed: JP232.2, JP233.2, R281.2, U167.1
unnamed: R284.1, U160.4, U168.3
unnamed: R283.2, U160.2
unnamed: R282.1, U160.6
unnamed: JP234.2, JP235.2, R284.2, U168.1
unnamed: R287.1, U161.4, U169.3
unnamed: R286.2, U161.2
unnamed: R285.1, U161.6
unnamed: JP236.2, JP237.2, R287.2, U169.1
unnamed: R290.1, U162.4, U170.3
unnamed: R289.2, U162.2
unnamed: R288.1, U162.6
unnamed: JP238.2, JP239.2, R290.2, U170.1
unnamed: R293.1, U163.4, U171.3
unnamed: R292.2, U163.2
unnamed: R291.1, U163.6
unnamed: JP240.2, JP241.2, R293.2, U171.1
unnamed: SJ18.1, U4-DNP8.17
unnamed: R271.2, R272.1, RA8.P$1, RB8.P$2, U156.1
RAW: C1.1, S1.2, S1.5, SJ1.1, U1.3, U2.1, U2.3
RAW1: C12.1, S5.2, S5.5, SJ3.1, U21.1, U21.3, U23.3
RAW2: C19.1, S8.2, S8.5, SJ5.1, U40.1, U40.3, U42.3
RAW3: C26.1, S11.2, S11.5, SJ7.1, U59.1, U59.3, U61.3
RAW4: C33.1, S14.2, S14.5, SJ9.1, U78.1, U78.3, U80.3
RAW5: C40.1, S17.2, S17.5, SJ11.1, U97.1, U97.3, U99.3
RAW6: C47.1, S20.2, S20.5, SJ13.1, U116.1, U116.3, U118.3
RAW7: C54.1, S23.2, S23.5, SJ15.1, U135.1, U135.3, U137.3
RAW8: C61.1, S26.2, S26.5, SJ17.1, U154.1, U154.3, U156.3
RST: C5.2, JP5.5, R8.1, S2.1, U3.29
RST1: C10.2, JP28.5, R36.1, S4.1, U4.29
RST2: C17.2, JP55.5, R69.1, S7.1, U39.29
RST3: C24.2, JP82.5, R102.1, S10.1, U58.29
RST4: C31.2, JP109.5, R135.1, S13.1, U77.29
RST5: C38.2, JP136.5, R168.1, S16.1, U96.29
RST6: C45.2, JP163.5, R201.1, S19.1, U115.29
RST7: C52.2, JP190.5, R234.1, S22.1, U134.29
RST8: C59.2, JP217.5, R267.1, S25.1, U153.29
RXI: S3.P, U3.30
RXI1: S6.P, U4.30
RXI2: S9.P, U39.30
RXI3: S12.P, U58.30
RXI4: S15.P, U77.30
RXI5: S18.P, U96.30
RXI6: S21.P, U115.30
RXI7: S24.P, U134.30
RXI8: S27.P, U153.30
RXI_FTDI: R3.1, R4.2, S3.S
RXI_FTDI1: R63.2, R64.1, S6.S
RXI_FTDI2: R96.2, R97.1, S9.S
RXI_FTDI3: R129.2, R130.1, S12.S
RXI_FTDI4: R162.2, R163.1, S15.S
RXI_FTDI5: R195.2, R196.1, S18.S
RXI_FTDI6: R228.2, R229.1, S21.S
RXI_FTDI7: R261.2, R262.1, S24.S
RXI_FTDI8: R294.2, R295.1, S27.S
RXI_XBEE: S3.O, U4-DNP.2
RXI_XBEE1: S6.O, U4-DNP1.2
RXI_XBEE2: S9.O, U4-DNP2.2
RXI_XBEE3: S12.O, U4-DNP3.2
RXI_XBEE4: S15.O, U4-DNP4.2
RXI_XBEE5: S18.O, U4-DNP5.2
RXI_XBEE6: S21.O, U4-DNP6.2
RXI_XBEE7: S24.O, U4-DNP7.2
RXI_XBEE8: S27.O, U4-DNP8.2
SCK: JP4.5, JP5.3, R9.2, U3.17
SCK1: JP28.3, JP32.5, R35.2, U4.17
SCK2: JP55.3, JP59.5, R68.2, U39.17
SCK3: JP82.3, JP86.5, R101.2, U58.17
SCK4: JP109.3, JP113.5, R134.2, U77.17
SCK5: JP136.3, JP140.5, R167.2, U96.17
SCK6: JP163.3, JP167.5, R200.2, U115.17
SCK7: JP190.3, JP194.5, R233.2, U134.17
SCK8: JP217.3, JP221.5, R266.2, U153.17
TXO: JP3.RXI, U3.31, U4-DNP.3
TXO1: JP31.RXI, U4.31, U4-DNP1.3
TXO2: JP58.RXI, U4-DNP2.3, U39.31
TXO3: JP85.RXI, U4-DNP3.3, U58.31
TXO4: JP112.RXI, U4-DNP4.3, U77.31
TXO5: JP139.RXI, U4-DNP5.3, U96.31
TXO6: JP166.RXI, U4-DNP6.3, U115.31
TXO7: JP193.RXI, U4-DNP7.3, U134.31
TXO8: JP220.RXI, U4-DNP8.3, U153.31
VBATT: JP1.1, JP25.2, S1.1, S1.4
VBATT1: JP33.2, JP36.1, S5.1, S5.4
VBATT2: JP60.2, JP63.1, S8.1, S8.4
VBATT3: JP87.2, JP90.1, S11.1, S11.4
VBATT4: JP114.2, JP117.1, S14.1, S14.4
VBATT5: JP141.2, JP144.1, S17.1, S17.4
VBATT6: JP168.2, JP171.1, S20.1, S20.4
VBATT7: JP195.2, JP198.1, S23.1, S23.4
VBATT8: JP222.2, JP225.1, S26.1, S26.4
VCC: C3.A, C4.1, C6.1, C7.1, JP2.2, JP4.8, JP5.2, R7.2, R8.2, U2.5, U3.4, U3.6, U3.18, U3.20, U4-DNP.1
VCC1: C8.1, C9.A, C11.1, C14.1, JP28.2, JP32.8, JP53.2, R34.2, R36.2, U4.4, U4.6, U4.18, U4.20, U4-DNP1.1, U21.5
VCC2: C15.1, C16.A, C18.1, C21.1, JP55.2, JP59.8, JP80.2, R67.2, R69.2, U4-DNP2.1, U39.4, U39.6, U39.18, U39.20, U40.5
VCC3: C22.1, C23.A, C25.1, C28.1, JP82.2, JP86.8, JP107.2, R100.2, R102.2, U4-DNP3.1, U58.4, U58.6, U58.18, U58.20, U59.5
VCC4: C29.1, C30.A, C32.1, C35.1, JP109.2, JP113.8, JP134.2, R133.2, R135.2, U4-DNP4.1, U77.4, U77.6, U77.18, U77.20, U78.5
VCC5: C36.1, C37.A, C39.1, C42.1, JP136.2, JP140.8, JP161.2, R166.2, R168.2, U4-DNP5.1, U96.4, U96.6, U96.18, U96.20, U97.5
VCC6: C43.1, C44.A, C46.1, C49.1, JP163.2, JP167.8, JP188.2, R199.2, R201.2, U4-DNP6.1, U115.4, U115.6, U115.18, U115.20, U116.5
VCC7: C50.1, C51.A, C53.1, C56.1, JP190.2, JP194.8, JP215.2, R232.2, R234.2, U4-DNP7.1, U134.4, U134.6, U134.18, U134.20, U135.5
VCC8: C57.1, C58.A, C60.1, C63.1, JP217.2, JP221.8, JP242.2, R265.2, R267.2, U4-DNP8.1, U153.4, U153.6, U153.18, U153.20, U154.5

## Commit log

2013-09-04 Initial repo commit
2013-09-04 Update README.md
    Added basic board description.
2014-02-18 Version 2.1 hardware files
2014-02-18 Fixing versions to 2.2
2014-02-19 Fixing airwire
2014-02-26 changed fiducials
2014-05-06 Adding Schottky diode to 5VUSB line for feedback protection
2014-05-06 Adding in switch for FTDI/XBee selection
2014-05-06 Very minor adjustments
    Fixed misaligned text in bplace (probably old)
    Minor routing tweaks to switch pads (centered trc)
    Renamed switch from U$3 to S3 (lib problem)
    Reduced R9 to 470 to brighten green LED2
2014-11-12 Updates to V2.3
    > Swapped LED resistors LED1 (green) now has 470, LED2 (red) now has 1K
    > Added heatsink pours for 3.3V reg U2
    > Reworked FTDI/XBEE switch, throw is now in direction of respective
    connectors, swapped silk, added silk to bottom
2014-11-20 Updating parts to proper libraries, swapped stat LED to blue
2014-11-26 Fixing issues from QC check
2014-11-26 Putting all measurements on one layer
2015-01-06 Updated Logos and Solder Jumper package
    The logos had polygons with zero-width lines (causing CAM error). The
    Solder Jumper was also causing error. Updated in library as well.
2015-01-25 Adding Code for Wireless Control of EL Sequencer
    Adding example sketch code to wirelessly control EL Sequencer w/ a
    remote Arduino to control the channels. Using XBee Series 1.
2015-02-05 Bumping up drill hits in side smd switch
2015-02-12 Fixing Redboard errors, updating atmega pkg, deleting tvalue name
2015-02-17 created panel v23
2015-04-14 Updating Arduino sketches for 1.6.3, updating README, modifying directory name
2015-04-14 Adding in comments on first example sketch
2017-06-01 Update README.md
    Remove the "test2" from the description.
2017-06-01 Update XBee_ELSequencer.ino
    Updating example link for chat since Digi changed their links.
2017-06-01 Update XBee_ELSequencer_Controller.ino
    Updating link to example since Digi updated their website.
2025-06-27 Update README.md
    Updating link
